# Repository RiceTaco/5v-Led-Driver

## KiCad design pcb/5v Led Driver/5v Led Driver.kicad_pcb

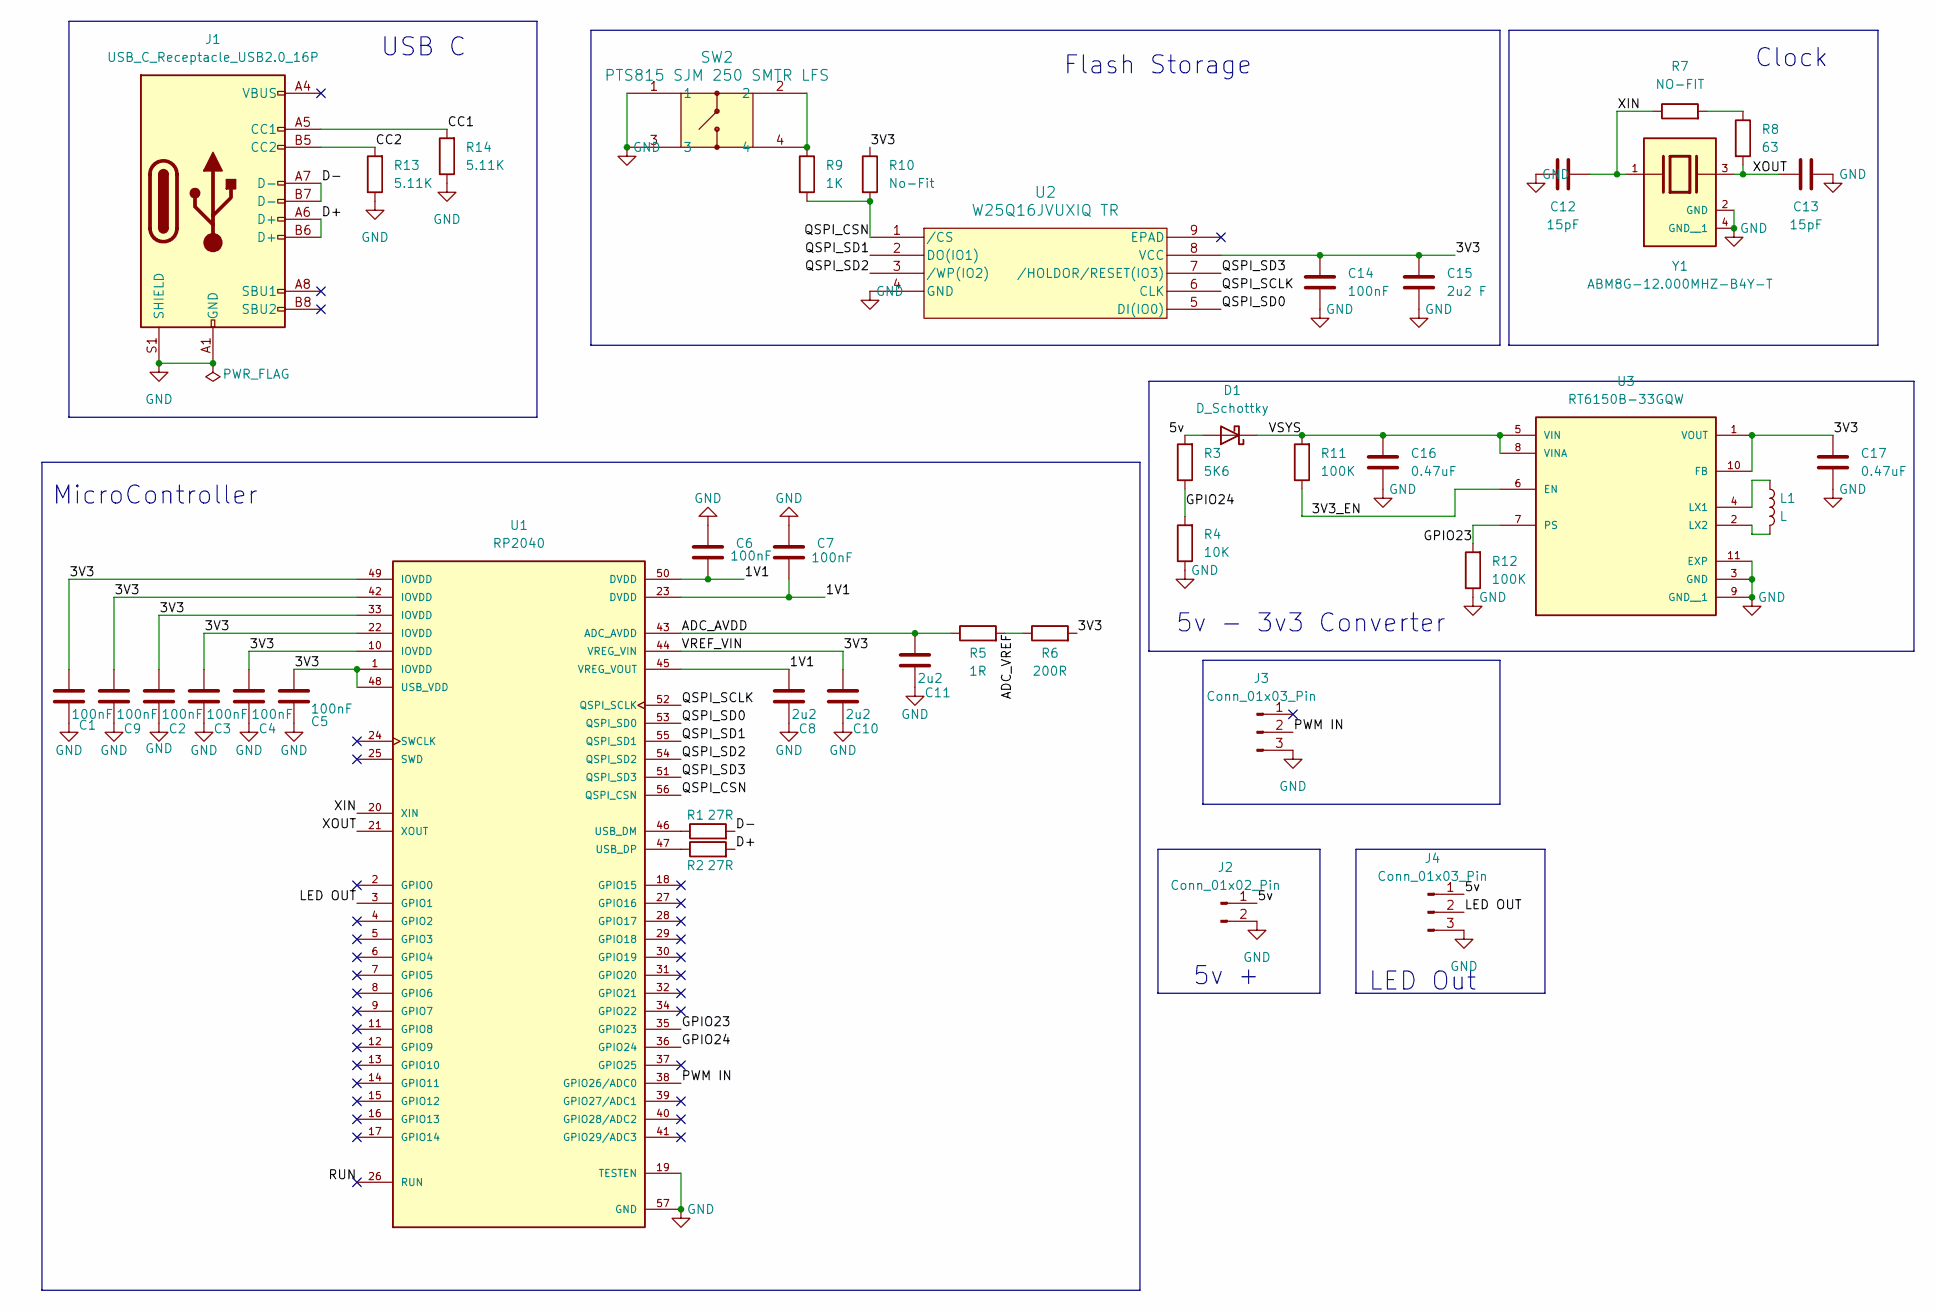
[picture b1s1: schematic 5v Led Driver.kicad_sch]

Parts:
C1, C2, C3, C4, C5, C6, C7, C9, C14: 100nF; C_0201_0603Metric
C8, C10, C11: 2u2; C_0201_0603Metric
C12, C13: 15pF; C_0201_0603Metric
C15: 2u2 F; C_0201_0603Metric
C16, C17: 0.47uF; C_0201_0603Metric
D1: D_Schottky; D_SOD-123F
J1: USB_C_Receptacle_USB2.0_16P; USB_C_Receptacle_G-Switch_GT-USB-7010ASV
J2: Conn_01x02_Pin; PinHeader_1x02_P2.54mm_Horizontal
J3, J4: Conn_01x03_Pin; PinHeader_1x03_P2.54mm_Horizontal
L1: L; L_0603_1608Metric
R1, R2: 27R; R_0201_0603Metric
R3: 5K6; R_0201_0603Metric
R4: 10K; R_0201_0603Metric
R5: 1R; R_0201_0603Metric
R6: 200R; R_0201_0603Metric
R7: NO-FIT; R_0201_0603Metric
R8: 63; R_0201_0603Metric
R9: 1K; R_0201_0603Metric
R10: No-Fit; R_0201_0603Metric
R11, R12: 100K; R_0201_0603Metric
R13, R14: 5.11K; R_0201_0603Metric
SW2: PTS815 SJM 250 SMTR LFS; SW4_PTS815 SJM 250 SMTR LFS_CNK
U1: RP2040; QFN-56-1EP_7x7mm_P0.4mm_EP3.2x3.2mm_ThermalVias; PARTREV 1.6.1
U2: W25Q16JVUXIQ TR; USON-8_UX_2x3x0p6_WIN
U3: RT6150B-33GQW; 10-WFDFN-EP_RIT; PARTREV July 2018
Y1: ABM8G-12.000MHZ-B4Y-T; CRYSTAL_ABM8G_ABR; PARTREV 08.13.15

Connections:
/1V1: C6.2, C7.2, C8.1, U1.23 (DVDD), U1.45 (VREG_VOUT), U1.50 (DVDD)
/3V3: C1.1, C2.1, C3.1, C4.1, C5.1, C9.1, C10.1, C14.1, C15.1, C17.1, R6.2, R10.1, U1.1 (IOVDD), U1.10 (IOVDD), U1.22 (IOVDD), U1.33 (IOVDD), U1.42 (IOVDD), U1.44 (VREG_VIN), U1.48 (USB_VDD), U1.49 (IOVDD), U2.8 (VCC), U3.1 (VOUT), U3.10 (FB)
/3V3_EN: R11.1, U3.6 (EN)
/5v: D1.2 (A), J2.1, J4.1, R3.2
/ADC_AVDD: C11.1, R5.1, U1.43 (ADC_AVDD)
/ADC_VREF: R5.2, R6.1
/CC1: J1.A5 (CC1), R14.2
/CC2: J1.B5 (CC2), R13.2
/D+: J1.A6 (D+), J1.B6 (D+), R2.2
/D-: J1.A7 (D-), J1.B7 (D-), R1.2
/GPIO23: R12.2, U1.35 (GPIO23), U3.7 (PS)
/GPIO24: R3.1, R4.2, U1.36 (GPIO24)
/LED OUT: J4.2, U1.3 (GPIO1)
/PWM IN: J3.2, U1.38 (GPIO26/ADC0)
/QSPI_CSN: R9.2, R10.2, U1.56 (QSPI_CSN), U2.1 (/CS)
/QSPI_SCLK: U1.52 (QSPI_SCLK), U2.6 (CLK)
/QSPI_SD0: U1.53 (QSPI_SD0), U2.5 (DI(IO0))
/QSPI_SD1: U1.55 (QSPI_SD1), U2.2 (DO(IO1))
/QSPI_SD2: U1.54 (QSPI_SD2), U2.3 (/WP(IO2))
/QSPI_SD3: U1.51 (QSPI_SD3), U2.7 (/HOLDOR/RESET(IO3))
/RUN: U1.26 (RUN)
/VSYS: C16.1, D1.1 (K), R11.2, U3.5 (VIN), U3.8 (VINA)
/XIN: C12.2, R7.1, U1.20 (XIN), Y1.1
/XOUT: C13.1, R8.2, U1.21 (XOUT), Y1.3
GND: C1.2, C2.2, C3.2, C4.2, C5.2, C6.1, C7.1, C8.2, C9.2, C10.2, C11.2, C12.1, C13.2, C14.2, C15.2, C16.2, C17.2, J1.A1 (GND), J1.A12 (GND), J1.B1 (GND), J1.B12 (GND), J1.S1 (SHIELD), J2.2, J3.3, J4.3, R4.1, R12.1, R13.1, R14.1, SW2.1, SW2.3, U1.19 (TESTEN), U1.57 (GND), U2.4 (GND), U3.3 (GND), U3.9 (GND__1), U3.11 (EXP), Y1.2 (GND), Y1.4 (GND__1)
unnamed: R7.2, R8.1
unnamed: R9.1, SW2.2, SW2.4
unnamed: R1.1, U1.46 (USB_DM)
unnamed: R2.1, U1.47 (USB_DP)
unnamed: L1.1, U3.4 (LX1)
unnamed: L1.2, U3.2 (LX2)

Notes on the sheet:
USB C
MicroController
Clock
5v - 3v3 Converter
LED Out
5v +
Flash Storage

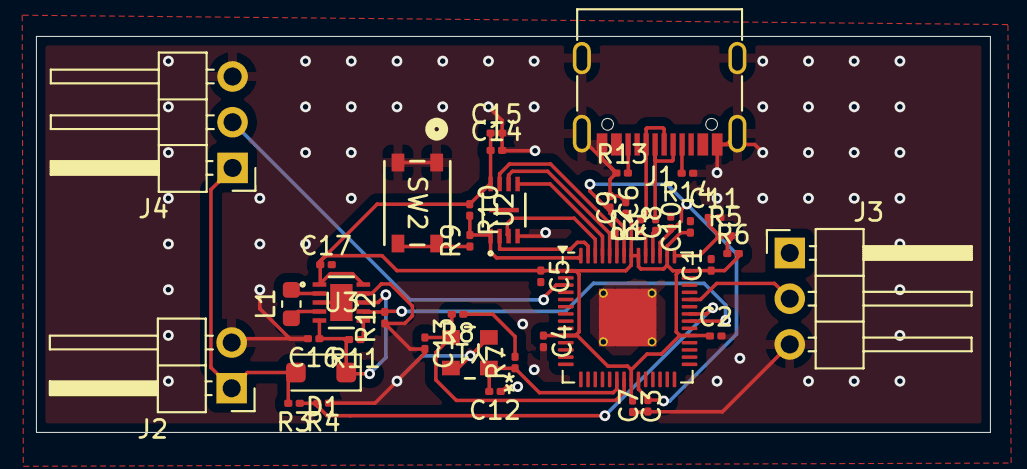
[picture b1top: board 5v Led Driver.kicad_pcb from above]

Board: 2 copper layers, 53.0 x 22.0 mm, 42 parts (0 on the bottom side), 30 nets.

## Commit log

2025-01-19 Create Block Diagram
2025-01-19 Rename Block Diagram.png to Block Diagram/Block Diagram.png
2025-01-21 Your commit message here
2025-02-02 good
2025-02-02 cant link pwmRead
2025-02-03 cant access pwmRead
2025-02-04 usbc mabye not good
2025-02-13 switched to micropython
2025-02-13 fixed file stackup
2025-02-13 wrote that function and added docs
